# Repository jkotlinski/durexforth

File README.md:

# durexforth

Modern C64 Forth. Includes a vi clone written in Forth, a high-resolution graphics library, plus MML music support.

[Latest Release](https://github.com/jkotlinski/durexforth/releases) :: [Manual](https://jkotlinski.github.io/durexforth/)

### Goals

* Fun. The system should be nice to work with on the real machine.
* Fast. DurexForth is the <a href=https://theultimatebenchmark.org/>fastest</a> C64 Forth, running at ~50x the speed of Basic V2!
* Easy to use. Implements the <a href=http://forth-standard.org/standard/words>Forth 2012</a> core standard, learn it with <a href=https://www.forth.com/starting-forth/>Starting Forth</a>!

### Testimonials

[C64 Programming May the Forth be with you Pt 1 - YouTube](https://www.youtube.com/watch?v=TXIDqptXmiM)

[C64 Programming Into the Forth Dimension Pt 2 - YouTube](https://www.youtube.com/watch?v=1oZztCmC8kc)

[A Brief Introduction to DurexForth for the Commodore 64](https://dev.to/ianwitham/a-brief-introduction-to-durexforth-for-the-commodore-64-1c99)

"Just fooling around but Durexforth is fast and fun!" -Kevin Reno

"Ich finde das Forth klein und effektiv, wunderbar." -Peter Bierbach

"Ist eine mächtige Sprache für ein 8-Bitter." -Pebisoft

"The author of durexForth was quite helpful... There is even a vim-like editor, impressive for being on a C64." -Christian Johansson

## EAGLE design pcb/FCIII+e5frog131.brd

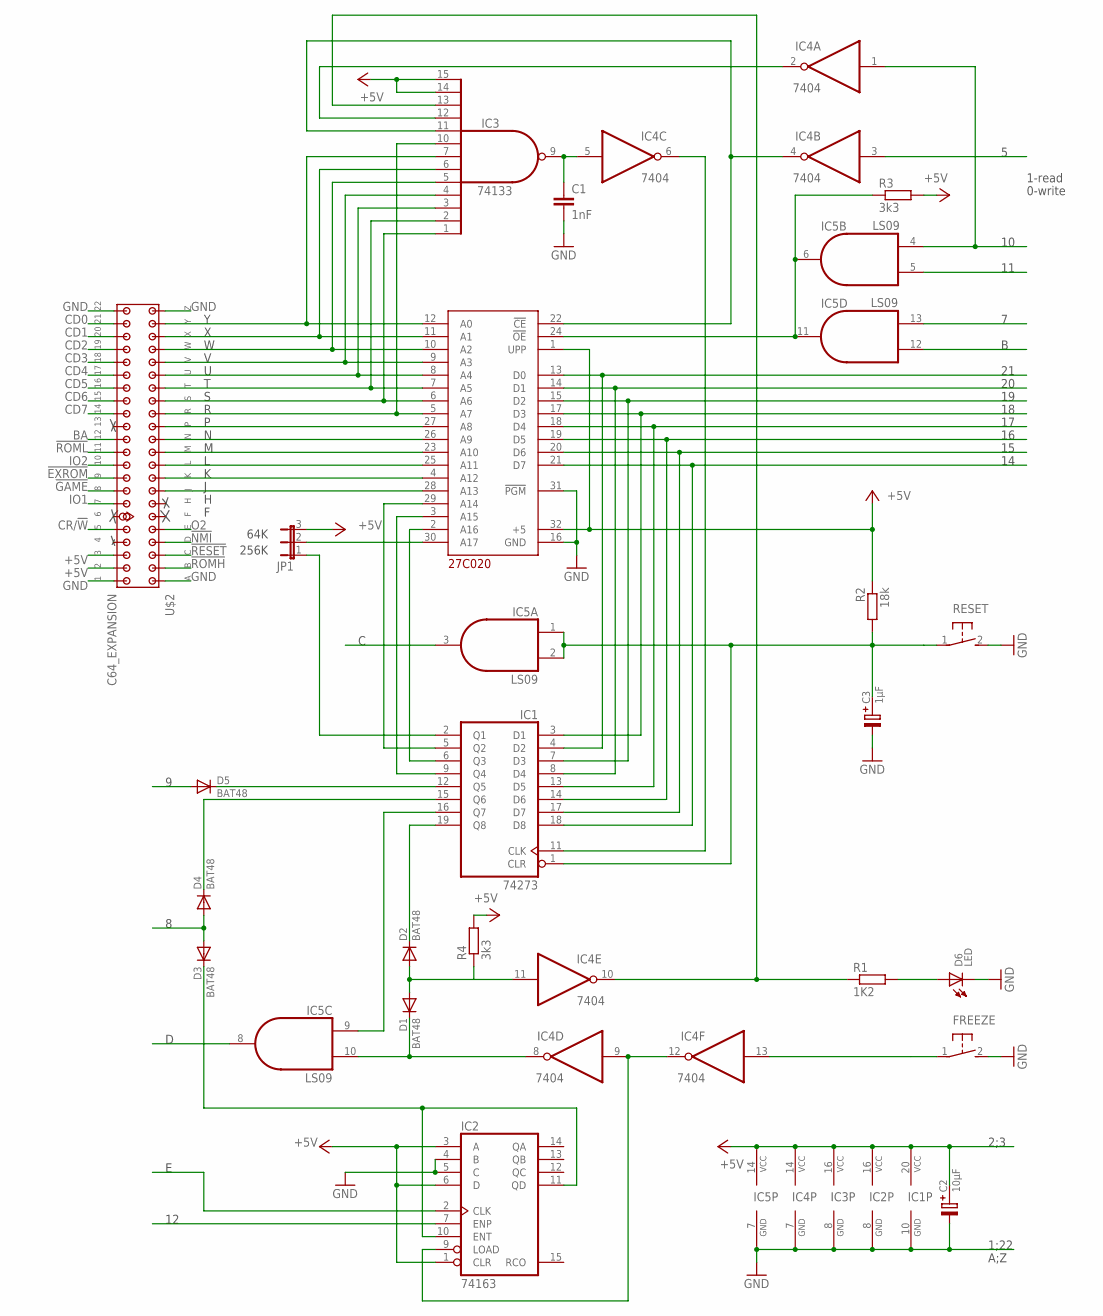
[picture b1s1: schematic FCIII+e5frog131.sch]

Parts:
C1: 1nF; C050-024X044
C2: 10µF; E1,6-4
C3: 1µF; E1,6-4
D1, D2, D3, D4, D5: BAT48; DO07
D6: LED; LED3E
FREEZE: 31-XX; B3F-31XX
IC1: 74273; DIL20
IC2: 74163; DIL16
IC3: 74133; DIL16
IC4: 7404; DIL14
IC5: LS09; DIL14
JP1: JP2E; JP2
R1: 1K2; 0207/10
R2: 18k; 0207/10
R3, R4: 3k3; 0207/10
RESET: 31-XX; B3F-31XX
U$1: 27C020; DIL32
U$2: C64_EXPANSION; EDGE44_254

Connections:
!EXROM: D5.A, U$2.P$9 (!EXROM)
!GAME: D3.A, D4.A, U$2.P$8 (!GAME)
!NMI: IC5.8 (O), U$2.D (!NMI)
!RESET: IC5.3 (O), U$2.C (!RESET)
!ROMH: IC5.12 (I0), U$2.B (!ROMH)
!ROML: IC5.5 (I1), U$2.P$11 (!ROML)
+5V: C2.+, IC1.20 (VCC), IC2.1 (CLR), IC2.3 (A), IC2.6 (D), IC2.16 (VCC), IC3.14 (I11), IC3.15 (I12), IC3.16 (VCC), IC4.14 (VCC), IC5.14 (VCC), JP1.3, R2.1, R3.2, R4.2, U$1.1 (UPP), U$1.32 (+5), U$2.P$2 (+5V_2), U$2.P$3 (+5V_3)
BA: IC2.7 (ENP), U$2.P$12 (BA)
CA0: IC3.7 (I6), U$1.12 (A0), U$2.Y (A0)
CA1: IC3.6 (I5), U$1.11 (A1), U$2.X (A1)
CA2: IC3.5 (I4), U$1.10 (A2), U$2.W (A2)
CA3: IC3.4 (I3), U$1.9 (A3), U$2.V (A3)
CA4: IC3.3 (I2), U$1.8 (A4), U$2.U (A4)
CA5: IC3.2 (I1), U$1.7 (A5), U$2.T (A5)
CA6: IC3.1 (I0), U$1.6 (A6), U$2.S (A6)
CA7: IC3.10 (I7), U$1.5 (A7), U$2.R (A7)
CA8: U$1.27 (A8), U$2.P (A8)
CA9: U$1.26 (A9), U$2.N (A9)
CA10: U$1.23 (A10), U$2.M (A10)
CA11: U$1.25 (A11), U$2.L (A11)
CA12: U$1.4 (A12), U$2.K (A12)
CA13: U$1.28 (A13), U$2.J (A13)
CD0: IC1.4 (D2), U$1.13 (D0), U$2.P$21 (D0)
CD1: IC1.8 (D4), U$1.14 (D1), U$2.P$20 (D1)
CD2: IC1.7 (D3), U$1.15 (D2), U$2.P$19 (D2)
CD3: IC1.3 (D1), U$1.17 (D3), U$2.P$18 (D3)
CD4: IC1.13 (D5), U$1.18 (D4), U$2.P$17 (D4)
CD5: IC1.14 (D6), U$1.19 (D5), U$2.P$16 (D5)
CD6: IC1.17 (D7), U$1.20 (D6), U$2.P$15 (D6)
CD7: IC1.18 (D8), U$1.21 (D7), U$2.P$14 (D7)
CR/!W: IC4.3 (I), U$2.P$5 (R!W)
FREEZE: FREEZE.1, IC4.13 (I)
GND: C1.2, C2.-, C3.-, D6.K, FREEZE.2 (S), IC1.10 (GND), IC2.4 (B), IC2.5 (C), IC2.8 (GND), IC3.8 (GND), IC4.7 (GND), IC5.7 (GND), RESET.2 (S), U$1.16 (GND), U$1.31 (!PGM), U$2.A (GND_A), U$2.P$1 (GND_1), U$2.P$22 (GND_22), U$2.Z (GND_Z)
IO1: IC5.13 (I1), U$2.P$7 (!IO1)
IO2: IC4.1 (I), IC5.4 (I0), U$2.P$10 (!IO2)
unnamed: IC2.9 (LOAD), IC4.9 (I), IC4.12 (O)
unnamed: D1.K, IC4.8 (O), IC5.10 (I1)
unnamed: IC1.16 (Q7), IC5.9 (I0)
unnamed: D3.K, IC2.10 (ENT), IC2.11 (QD)
unnamed: D5.K, IC1.12 (Q5)
unnamed: D1.A, D2.A, IC4.11 (I), R4.1
unnamed: D2.K, IC1.19 (Q8)
unnamed: D4.K, IC1.15 (Q6)
unnamed: IC1.6 (Q3), U$1.2 (A16)
unnamed: IC1.9 (Q4), U$1.3 (A15)
unnamed: IC1.5 (Q2), U$1.29 (A14)
unnamed: IC1.2 (Q1), JP1.1
unnamed: JP1.2, U$1.30 (A17)
unnamed: C1.1, IC3.9 (O), IC4.5 (I)
unnamed: IC1.11 (CLK), IC4.6 (O)
unnamed: IC3.11 (I8), IC4.4 (O), U$1.22 (!CE)
unnamed: IC3.12 (I9), IC4.2 (O)
unnamed: IC5.6 (O), IC5.11 (O), R3.1, U$1.24 (!OE)
unnamed: IC3.13 (I10), IC4.10 (O), R1.1
unnamed: D6.A, R1.2
O2: IC2.2 (CLK), U$2.E (PHI2)
RESET: C3.+, IC1.1 (CLR), IC5.1 (I0), IC5.2 (I1), R2.2, RESET.1

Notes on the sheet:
64K
256K
1;22
A;Z
1-read
0-write
2;3

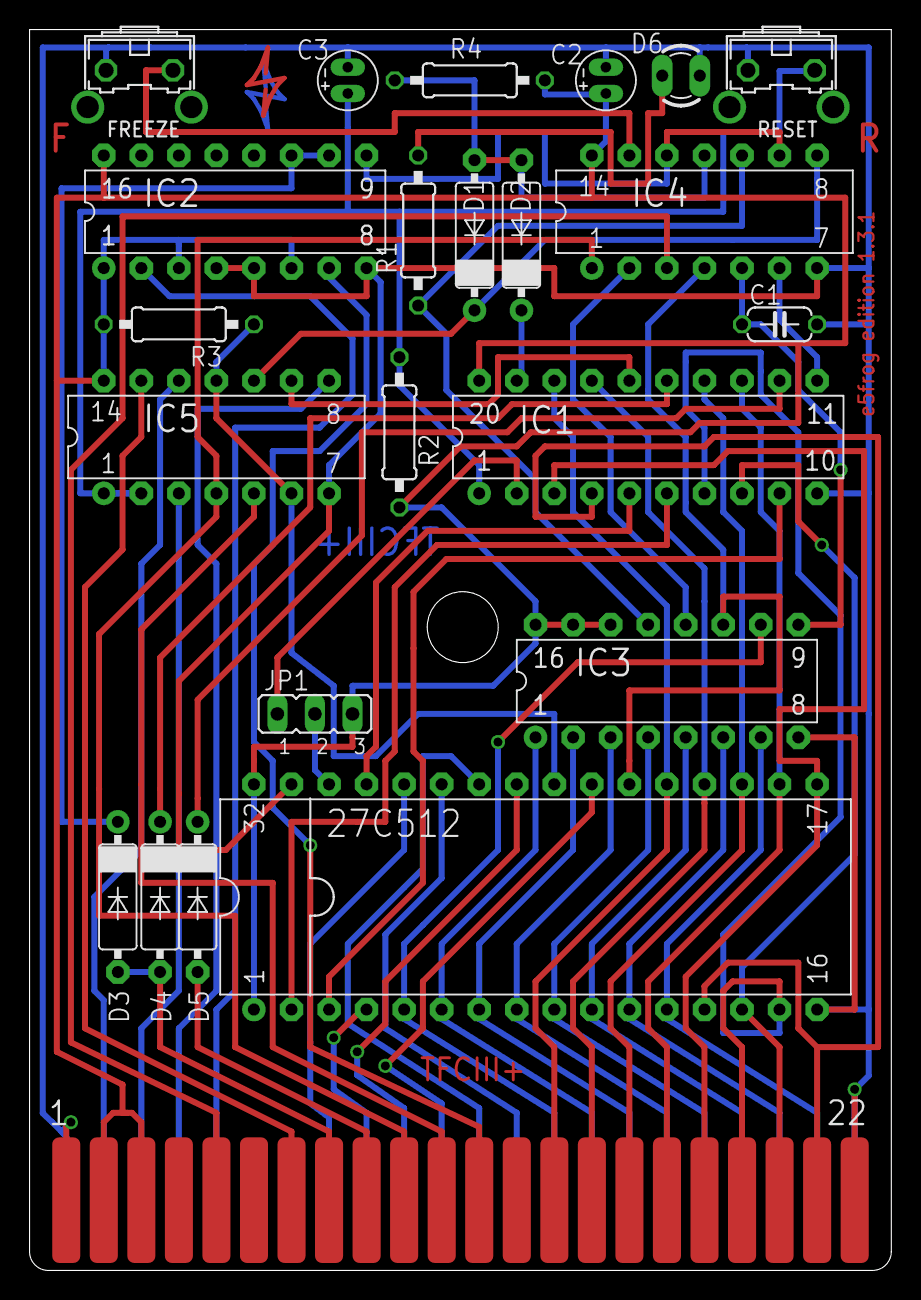
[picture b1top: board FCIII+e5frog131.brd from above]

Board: 2 copper layers, 58.3 x 84.0 mm, 23 parts (0 on the bottom side), 57 nets.

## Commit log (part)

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2022-08-21 remove LaTeX escapes
2022-08-21 make docs
2022-08-21 edit tutorial
2022-08-21 remove broken cross-references
2022-08-22 move *.asm to asm_src folder
2022-08-23 update MOVE from cc65 memmove.s, add license info
2022-08-23 add Forth Test Suite to LICENSE.txt
2022-08-28 doc: added comment re: double literals missing
2022-08-28 remove forth test suite comments, to free .d64 space
2022-09-06 fix weird ' implementation
2022-09-08 Minor edits of AsciiDoc manual
2022-09-08 Minor edits of AsciiDoc manual (#480)
2022-09-10 move test sources to their own folder
2022-09-10 added TRUE+FALSE+CORE EXT tests. closes #467
2022-09-11 remove dead sys.fs
2022-09-11 fix x
2022-12-17 v: allow inserting home+cursor chars inside quotes. closes #492
2022-12-18 v: fix cursor for inverted control characters
2022-12-18 Added check target, some clean-up
2022-12-18 Used old variable
2022-12-19 fix non-portable .prg header insertion
2022-12-19 avoid build/header file
2022-12-23 revive insert cursor movement. closes #496
2022-12-28 fix LOADB/SAVEB hang on device not present
    closes #499
2022-12-28 fix DOS hang on device not present
2022-12-28 move asm_src/forth_src to asm/forth
2022-12-28 move docs_src to manual
2023-01-12 doc: minimal tidy-up
2023-01-12 more accurate calculation
2023-01-12 bugfix marker
2023-01-13 fix undefined behavior after first-time boot
2023-01-13 edit changelog
2023-01-13 tidy up changelog
2023-01-15 Superfluous clrchn in SEND-CMD
    Default channels already set, Typing and seeing it in on screen. before calling ```send-cmd```
2023-01-15 Update CHANGELOG.md
    SEND-CMD: CLRCHN not required when current I/O channels are screen and keyboard.
2023-01-15 follow-up EVALUATE fix. closes #505
2023-01-15 CLRCHN after close_all_logical_files in interpreter.asm
    close_all_logical_files should call CLRCHN .
2023-01-15 close_all_logical_files should do CLRCHN first in disk.asm
    Like, so.
2023-01-15 Replace extraneous JMP CLRCHN in LOADB with RTS
    LOAD does not effect default devices
2023-01-16 Move close_all_logical_files: to interpreter.asm
    To inline with LOADB
2023-01-16 Note QUIT and LOADB changes
    - QUIT: moved and inlined close_all_logical_files
    - LOADB: Replace extraneous JMP CLRCHN with RTS
2023-01-16 make deploy now automatically exits Vice
    as advised by #312
2023-01-17 let `make deploy` run tests
2023-01-17 extracted accept to its own file
2023-01-22 remove deprecated Vice +confirmonexit
2023-01-22 limit "make deploy" cycle count to 2000000000
2023-01-22 try to break build on purpose
2023-01-22 test: purposefully fail build
2023-01-22 use apt-get instead of apt
2023-02-03 refer reader of included files to their includer
    Some of the .asm word list comments were out of date
    anyway, so I moved them into durexforth.asm, making
    it a single searchable index for the whole dictionary.
2023-02-03 durexforth.asm: assemble dictionary sentinel before program
    Saves a counter juggle.
2023-02-03 durexforth.asm: reformat and expand comments
    Forgot to apply PROGRAM_BASE earlier as well.
2023-02-03 capture screenshots and production artifacts
2023-02-03 tidy up artifact name
2023-02-04 don't put "ok" test file in root folder
2023-02-04 add script to verify .asm headers
2023-02-04 change message
2023-02-04 add comment
2023-02-04 move .asm header verify to deploy step
2023-02-04 normalize line endings (#516)
2023-02-04 renormalize
2023-02-04 assemble dictionary sentinel before program
    Saves a counter juggle.
2023-02-04 reformat and expand comments
2023-02-05 Just a few comments for new readers of the source (#517)
    * assemble dictionary sentinel before program
    Saves a counter juggle.
    * consolidate addresses and dictionary info
    * reformat and expand comments
2023-02-05 do not run fractals demo on include
2023-02-05 rewrite more code in assembly
2023-02-05 fix comments
2023-02-05 fix turtle BACK
2023-02-05 tiny optimization
2023-02-05 Optimize fractals (#519)
    * rewrite some turtle code in assembly
    * do not run fractals demo on include
    * rewrite more code in assembly
    * added temporary test code
    * fix comments
    * simplify turtle left/right
2023-02-05 tidy up
2023-02-06 added `compare`
2023-02-06 document `compare`.
2023-02-06 inline signum into compare
2023-02-06 whoops, `abort"` is a compiler word.
    Not sure if that's related to the extra `depth`
    in the check job though.
2023-02-14 Possible manual changes for IEC commands
    I thought I'd see if this was something we want to roll with before I do any more work.
    What do you think?
2023-02-15 Refine IEC docs
    Additional hints and elucidations.
2023-02-15 implement n>r , nr>
2023-02-15 polish docs some
    IEC stuff
2023-02-15 Further refinements
2023-02-18 Make === Protocol-Level IEC Device I/O header
2023-02-26 SEE code golf
2023-03-14 optimize `hold`
    Instead of moving characters forward, store them going backward.
2023-03-14 optimize `hold` (#531)
    Instead of moving characters forward, store them going backward.
2023-03-27 drop format.fs dependency on BASE=HEX
2023-04-15 temporary fix build
2023-04-16 added ERASE
2023-04-16 added PARSE
2023-04-16 standard S"
2023-04-16 disallow multi-line .(
2023-04-16 remove GETC
2023-04-16 simplify mml"
2023-04-16 moved mml" to mml.fs
2023-04-16 fix interpreted ( stack effect
2023-04-16 remove bad comment
2023-04-16 v f7: evaluate line-by-line
    because: \ now skips to end of input buffer
2023-04-19 split
2023-04-19 avoid "split nip"
2023-04-19 swap VALUE ldy/lda
2023-04-20 Revert "swap VALUE ldy/lda"
    This reverts commit a80201762fe4ef5b1f4726cb3c2e4096ccf1c4d6.
2023-04-20 added SPLIT, removed 100/ (#546)
    * split
    * avoid "split nip"
    * tidy up
    * swap VALUE ldy/lda
    * Revert "swap VALUE ldy/lda"
    This reverts commit a80201762fe4ef5b1f4726cb3c2e4096ccf1c4d6.
2023-04-21 renamed gfx ERASE=>PEN
2023-04-22 blocks
2023-04-22 drop least recently used buffer
2023-04-22 wipe block if file missing
2023-04-22 added BUFFER
2023-04-22 add empty-buffers
2023-04-22 added update
2023-04-22 simplify buffer management (no lru)
2023-04-22 drop path storage
2023-04-22 add TODO comment
2023-04-23 Move `pad`, `#>` after `here`
2023-04-23 Revert `pad`
2023-04-23 Fix `ls`.
2023-04-25 Update docs.
2023-04-26 Take `#>` space from `pad`. (#549)
    * Move `pad`, `#>` after `here`
    * Revert `pad`
    * Fix `see`.
    * Fix `ls`.
    * Revert to master, take `pad` space instead.
    * Update docs.
2023-04-27 fix empty-buffers
2023-04-28 added b-a to allocate blocks
2023-04-28 add create-blocks
2023-04-28 safer map loading
2023-04-28 factoring: extract word
2023-04-28 seemingly fixed block load
2023-04-28 tidy up; fix load-map error
2023-04-28 temporarily disable build
2023-04-29 added TODO comment
2023-04-29 move D+ >NUMBER from compat to base, document D+
    goal: facilitate blocks
2023-04-29 document D+
2023-04-29 simplify code
2023-04-29 simplify code (thx @ekipan!)
2023-04-29 bugfix load-blk
2023-04-29 add decimal for number formatting, tidy up
2023-04-29 save a byte
2023-04-30 made block numbers start at 1 again (standard)
2023-04-30 CHAR no longer does REFILL on missing text
2023-04-30 push/pop BLK
2023-05-01 start work on save/restore BLK
2023-05-01 some work on testing
2023-05-01 made test-load pass
2023-05-01 allocate 11 block buffers
2023-05-01 fix create-blocks
2023-05-01 fix: made LOADB restore current file
2023-05-02 fix viceutil. thx @ekipan
2023-05-05 Revert "v f7: evaluate line-by-line"
    This reverts commit c09c3c91957aa6beae928dc8fb80fd5db54197da.
2023-05-05 another attempt to resolve v F7
2023-05-06 increase input stack to eight levels
2023-05-07 added INCLUDE-RAM, use that for v F7
2023-05-07 update header
2023-05-07 code golf
2023-05-07 tweak whitespace
2023-05-07 drop redundant code
2023-05-07 remove INTERPRET
2023-05-07 another REFILL fix
2023-05-07 removed redundant interpret_loop
2023-05-07 repair EVALUATE
2023-05-08 rename INCLUDE-RAM => INCLUDE-STRING
2023-05-08 replace evaluate with multi-line evaluate
2023-05-08 update evaluate manual
2023-05-08 fix manual typography
2023-05-08 allow nesting EVALUATE calls
2023-05-13 allow lines longer than 256 bytes
2023-05-14 allow typing uppercase (whoops).
2023-05-15 space-optimize `accept` (#557)
    * space-optimize `accept`
    * allow typing uppercase (whoops).
    * (trivial) whitespace, comments, code order
2023-05-15 Multi-line EVALUATE (#556)
    * Revert "fix EVALUATE-BUFFER"
    This reverts commit 05eded9e30bfde1681b5c72ccdaa36c4932d6a90.
    * Revert "v f7: evaluate line-by-line"
    This reverts commit c09c3c91957aa6beae928dc8fb80fd5db54197da.
    * another attempt to resolve v F7
    * Revert "another attempt to resolve v F7"
2023-05-19 Revert "renamed ;CODE => END-CODE"
    This reverts commit 0efd415d37b6569240f3092d7f5db6f8aa2141fa.
2023-05-19 freeze headlessvice.deb
2023-05-20 optimize `CHAR_TO_LOWERCASE`
    Does only a single cmp instruction in the common case of characters less than 'A'.
2023-05-20 add END-CODE, remove ;CODE (#561)
    goal: improve conformance with forth-standard.org
2023-05-20 further optimize lowercase conversion
2023-05-21 fix `'` not showing name if missing
2023-05-21 Fix tick (#563)
    * fix `'` not showing name if missing
    * ...
2023-05-30 abort with error on empty HEADER name
2023-05-31 Print "err" instead.
    Also moved W2 code up to not repeat the INX instructions.
2023-06-23 Update memmap.adoc typo
    durexForth not DurexForth
2023-08-07 Update words.adoc typos I introduced. (#566)
2024-11-19 abort with error on empty HEADER name (#564)
    * abort with error on empty HEADER name
    * changelog
    * Print "err" instead.
    Also moved W2 code up to not repeat the INX instructions.
2024-11-19 updated changelog
2024-12-14 bump headless vice to 3.8
2024-12-14 try installing libportaudio
2024-12-14 bump headless vice to 3.8 (#580)
    * bump headless vice to 3.8
    * try installing libportaudio
    * libportaudio2
2024-12-14 factor out `aborts` #579
2024-12-15 rename to (abort")
2024-12-15 factor out `aborts` #579 (#581)
    * factor out `aborts` #579
    * rename to (abort")
    * spelling
2024-12-15 added testexception test suite
2024-12-15 implement catch
2024-12-15 Fixed minor typos (#582)
    * Update words.adoc
    * Update iec.fs
    * Update testcore.fs
2024-12-15 add abort, abort"
2024-12-15 almost working
2024-12-16 try restoring input sources... not there yet
2024-12-16 remove set-error-count call
2024-12-22 optimize LIT
2024-12-22 optimize LIT (#585)
2024-12-22 optimize -1
2024-12-22 only use git tag for version string
    The goal is to make memory layout more stable, as the version string
    length now depends less on local git status.
2024-12-22 update docs
2024-12-22 reset HANDLER on QUIT
2024-12-22 refactoring: rename variable
2024-12-22 seems to work a little
2024-12-22 rename label
2024-12-22 tweak error message
2024-12-22 add divison by zero exception
2024-12-23 hook up user interrupt to exceptions
2024-12-24 document exceptions
2024-12-24 update comment
2024-12-24 Update words.adoc
    Fixed typo of stack diagramming of IEC words. Also considering IEC words use default device rather than stack input.
2024-12-25 IEC documentation edit (#591)
    * Update words.adoc
    Fixed typo of stack diagramming of IEC words. Also considering IEC words use default device rather than stack input.
    * Only the examples require io
    It should be clear that iec routines don't require io, nor do they touch $BA, although the examples do.
2024-12-25 fix manual formatting of immediate keyword
2024-12-26 added catch example
2024-12-26 document 0>
2024-12-26 update ioabort docs
2024-12-27 Revert "remove unneeded github CI dependency"
    This reverts commit be8aa7dbef10d65b228a09a4cc8aa70c7bb0d6f7.
2024-12-27 fixes
2024-12-27 micro optimize
2024-12-27 print unknown exception numbers
2024-12-27 remove STRING, - it is not needed
